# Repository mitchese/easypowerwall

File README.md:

easypowerwall
=============

There are many projects which are building battery packs out of 18650 cells and fusable links. These
projects all require massive amounts of labour to solder or weld the packs together. Once built, a dead
cell in the pack requires much work to re-build the pack. This project will make an 18650 sandwich,
with PCBs on either side taking care of the boring solder work. If a cell dies or the pack must be re-built,
then four bolts hold it together and the cells are then replaceable.

The packs are designed around a 13s12p configuration - 13 in series and up to 12 in parallel. This will make
a 48v pack. The spacing is designed around these holders:

.

Create a matrix of 13x12 cells, with the rows alternating positive/negative. :warning: Pay attention to the polarity :warning:
Then sandwich a PCB on either side of the board and you're done.

Materials Required
==================

Each 48v pack will require:

Qty | Item | Sample Source
--- | ------------- | -----------
2 | PCBs | Upload the Gerbers/<release>.zip to JLCPCB
156 | 18650 Cells | Buy a tesla and recover them from the pack
312 | Battery Springs | https://www.ebay.de/sch/i.html?_from=R40&_nkw=battery+spring&_sacat=0&rt=nc&LH_PrefLoc=2
4 | M5x90 Nylon Bolts + nuts | TBD
21 | Pin headers | TBD
1 | BMS | Daly 13S LiIon BMS
1 | BMS DIY Cable
2 | M5 Nuts + Bolts - Metal for poles

Assembly
========

Todo once order arrives

BMS DIY Cable
=============

The circuit board is designed such that the top and bottom can be the same board. Because of this, the BMS connector on
the bottom borard needs to be connected to the even connectors on the top board. The pinouts are as follows

BMS Connector bottom | Input top
-------------------- | ---------
1 | 2
3 | 4
5 | 6
7 | 8
9 | 10
11 | 12
13 | 14

Repairing Fuses
===============

The board has a fuse per cell, as well as one fuse per balancing input from the BMS. If a PCB trace fuse blows,
the board can be fixed by soldering a fuse wire inbetween the two pads.

Fuse | JLCPCB Current 1oz
---- | ------------------
Battery | TODO
Balancer | TODO

TODO: Measure the acutal fuse performance
TODO: Add pictures of fuse repair

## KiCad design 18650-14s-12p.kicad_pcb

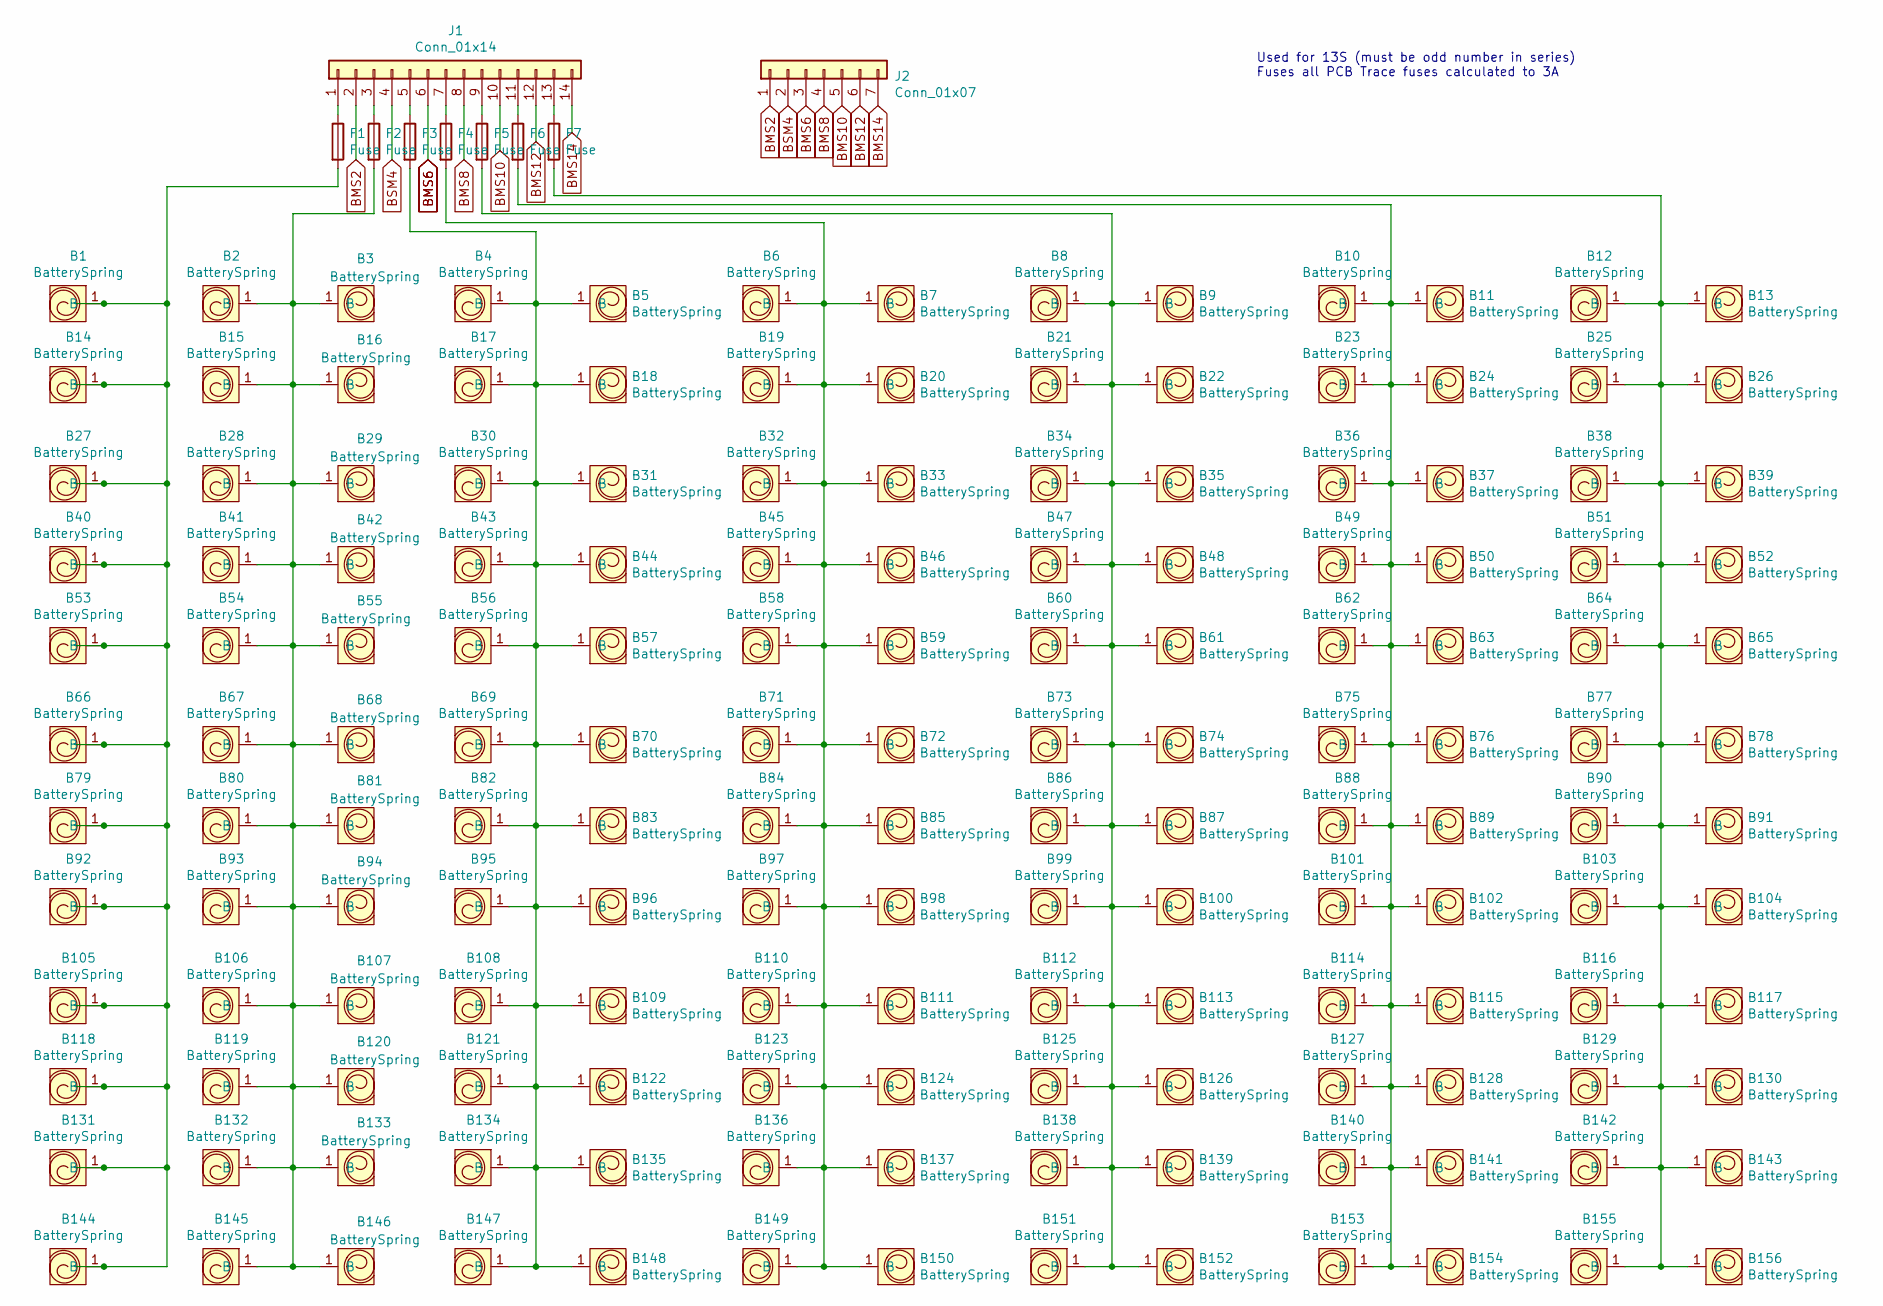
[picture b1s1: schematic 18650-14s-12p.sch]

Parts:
B1, B2, B3, B4, B5, B6, B7, B8, B9, B10, B11, B12, B13, B14, B15, B16, B17, B18, B19, B20, B21, B22, B23, B24, B25, B26, B27, B28, B29, B30, B31, B32, B33, B34, B35, B36, B37, B38, B39, B40, B41, B42, B43, B44, B45, B46, B47, B48, B49, B50, B51, B52, B53, B54, B55, B56, B57, B58, B59, B60, B61, B62, B63, B64, B65, B66, B67, B68, B69, B70, B71, B72, B73, B74, B75, B76, B77, B78, B79, B80, B81, B82, B83, B84, B85, B86, B87, B88, B89, B90, B91, B92, B93, B94, B95, B96, B97, B98, B99, B100, B101, B102, B103, B104, B105, B106, B107, B108, B109, B110, B111, B112, B113, B114, B115, B116, B117, B118, B119, B120, B121, B122, B123, B124, B125, B126, B127, B128, B129, B130, B131, B132, B133, B134, B135, B136, B137, B138, B139, B140, B141, B142, B143, B144, B145, B146, B147, B148, B149, B150, B151, B152, B153, B154, B155, B156: BatterySpring; batteryspring
F1, F2, F3, F4, F5, F6, F7: Fuse; pcbfuse_4a
J1: Conn_01x14; PinHeader_1x14_P2.54mm_Vertical
J2: Conn_01x07; PinHeader_1x07_P2.54mm_Vertical

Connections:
BMS2: J1.2, J2.1
BMS6: J1.6, J2.3
BMS8: J1.8, J2.4
BMS10: J1.10, J2.5
BMS12: J1.12, J2.6
BMS14: J1.14, J2.7
BSM4: J1.4, J2.2
unnamed: B1.1, B14.1, B27.1, B40.1, B53.1, B66.1, B79.1, B92.1, B105.1, B118.1, B131.1, B144.1, F1.2
unnamed: B10.1, B11.1, B23.1, B24.1, B36.1, B37.1, B49.1, B50.1, B62.1, B63.1, B75.1, B76.1, B88.1, B89.1, B101.1, B102.1, B114.1, B115.1, B127.1, B128.1, B140.1, B141.1, B153.1, B154.1, F6.2
unnamed: B8.1, B9.1, B21.1, B22.1, B34.1, B35.1, B47.1, B48.1, B60.1, B61.1, B73.1, B74.1, B86.1, B87.1, B99.1, B100.1, B112.1, B113.1, B125.1, B126.1, B138.1, B139.1, B151.1, B152.1, F5.2
unnamed: B12.1, B13.1, B25.1, B26.1, B38.1, B39.1, B51.1, B52.1, B64.1, B65.1, B77.1, B78.1, B90.1, B91.1, B103.1, B104.1, B116.1, B117.1, B129.1, B130.1, B142.1, B143.1, B155.1, B156.1, F7.2
unnamed: B2.1, B3.1, B15.1, B16.1, B28.1, B29.1, B41.1, B42.1, B54.1, B55.1, B67.1, B68.1, B80.1, B81.1, B93.1, B94.1, B106.1, B107.1, B119.1, B120.1, B132.1, B133.1, B145.1, B146.1, F2.2
unnamed: B4.1, B5.1, B17.1, B18.1, B30.1, B31.1, B43.1, B44.1, B56.1, B57.1, B69.1, B70.1, B82.1, B83.1, B95.1, B96.1, B108.1, B109.1, B121.1, B122.1, B134.1, B135.1, B147.1, B148.1, F3.2
unnamed: B6.1, B7.1, B19.1, B20.1, B32.1, B33.1, B45.1, B46.1, B58.1, B59.1, B71.1, B72.1, B84.1, B85.1, B97.1, B98.1, B110.1, B111.1, B123.1, B124.1, B136.1, B137.1, B149.1, B150.1, F4.2
unnamed: F1.1, J1.1
unnamed: F2.1, J1.3
unnamed: F3.1, J1.5
unnamed: F4.1, J1.7
unnamed: F5.1, J1.9
unnamed: F6.1, J1.11
unnamed: F7.1, J1.13

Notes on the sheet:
Used for 13S (must be odd number in series) Fuses all PCB Trace fuses calculated to 3A

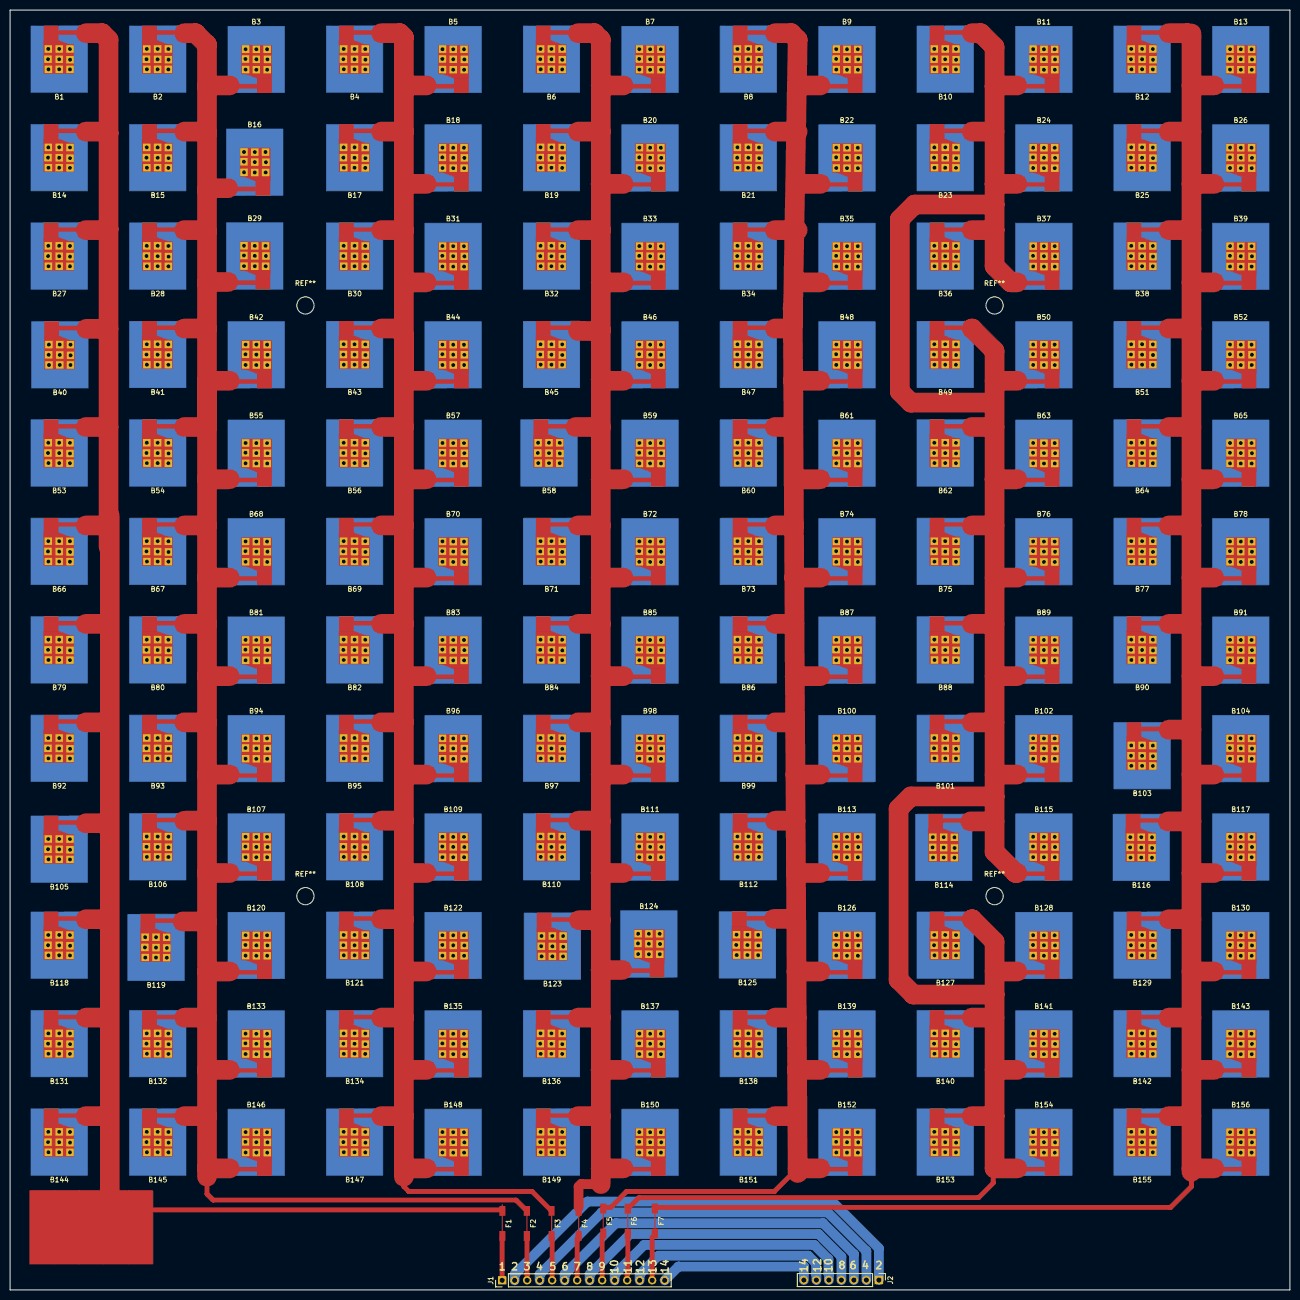
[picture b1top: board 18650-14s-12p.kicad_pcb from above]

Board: 2 copper layers, 260.0 x 260.0 mm, 165 parts (0 on the bottom side), 21 nets.

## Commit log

2020-03-19 13s3p with fuse initial commit
2020-03-20 Updated to 13s-12p
2020-03-21 Changes for v0.1-rc
2020-03-21 Rename project
2020-03-21 Add gerbers from 0.1-rc; Sent to jlcpcb
2020-03-21 Add readme
